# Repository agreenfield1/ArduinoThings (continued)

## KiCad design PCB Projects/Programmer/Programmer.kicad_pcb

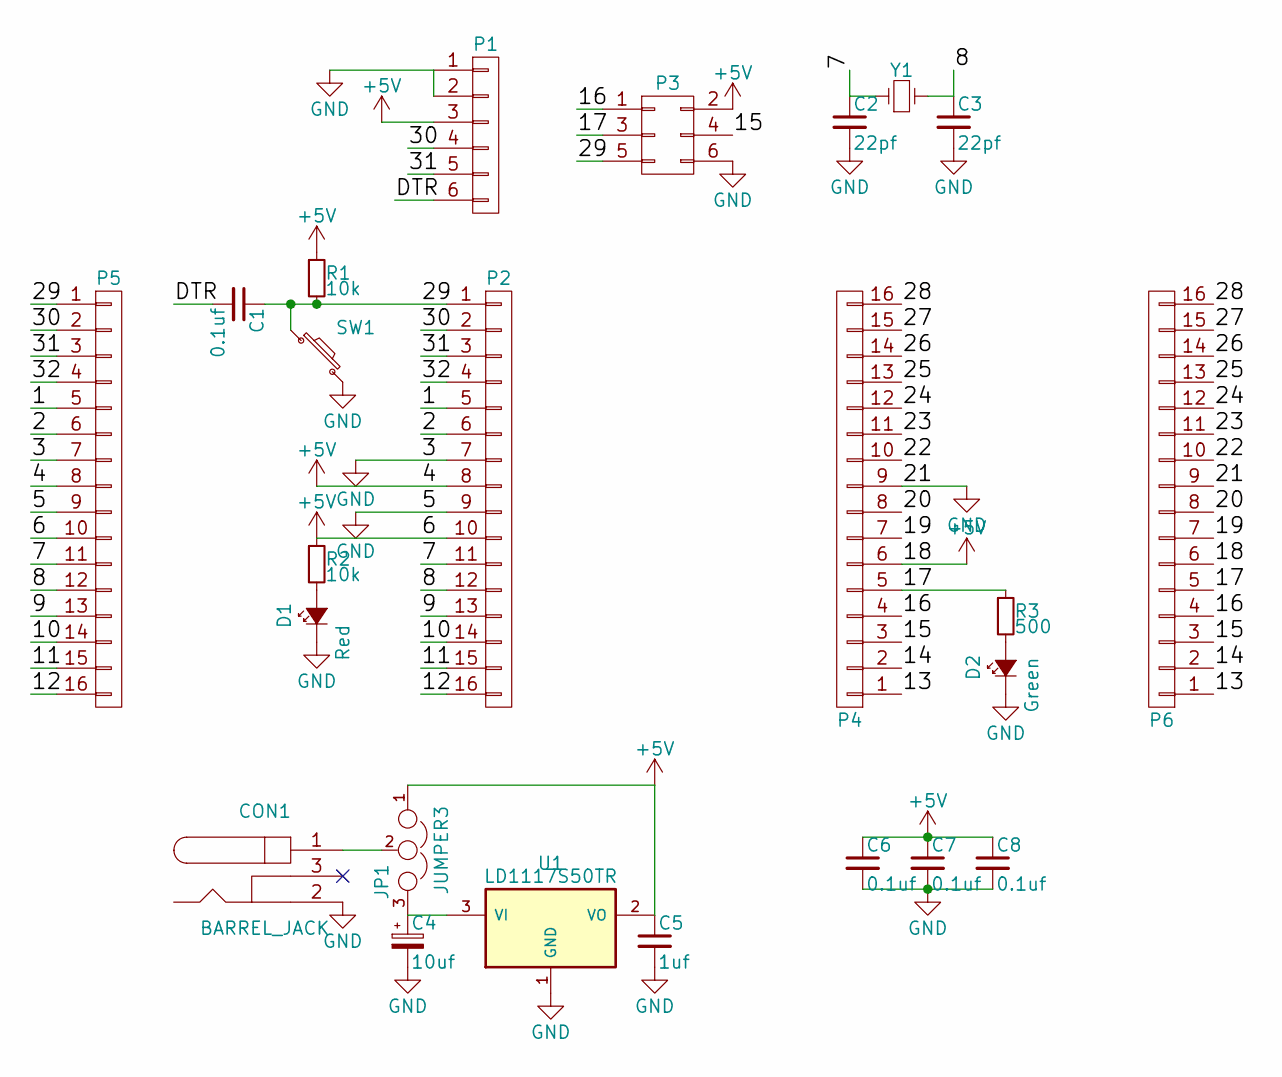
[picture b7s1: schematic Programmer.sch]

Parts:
C1, C6, C7, C8: 0.1uf; C_1206_HandSoldering
C2, C3: 22pf; C_1206_HandSoldering
C4: 10uf; TantalC_SizeA_EIA-3216_HandSoldering
C5: 1uf; C_1206_HandSoldering
CON1: BARREL_JACK; DC-Jack
D1: Red; LED_1206
D2: Green; LED_1206
JP1: JUMPER3; Pin_Header_Straight_1x03
P1: CONN_01X06; Pin_Header_Straight_1x06
P2, P4, P5, P6: CONN_01X16; Pin_Header_Straight_1x16
P3: CONN_02X03; Pin_Header_Straight_2x03
R1, R2: 10k; R_1206_HandSoldering
R3: 500; R_1206_HandSoldering
SW1: SW_PUSH_SMALL; Pin_Header_Angled_1x02
U1: LD1117S50TR; SOT-223
Y1: 22pf; Crystal_HC49-U_Vertical

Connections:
+5V: C5.1, C6.1, C7.1, C8.1, JP1.1, P1.3, P2.8, P2.10, P3.2, P4.6, P5.8, P5.10, P6.6, R1.1, R2.1, U1.2 (VO)
/1: P2.5, P5.5
/2: P2.6, P5.6
/7: C2.1, P2.11, P5.11, Y1.1
/8: C3.1, P2.12, P5.12, Y1.2
/9: P2.13, P5.13
/10: P2.14, P5.14
/11: P2.15, P5.15
/12: P2.16, P5.16
/13: P4.1, P6.1
/14: P4.2, P6.2
/15: P3.4, P4.3, P6.3
/16: P3.1, P4.4, P6.4
/17: P3.3, P4.5, P6.5, R3.1
/19: P4.7, P6.7
/20: P4.8, P6.8
/22: P4.10, P6.10
/23: P4.11, P6.11
/24: P4.12, P6.12
/25: P4.13, P6.13
/26: P4.14, P6.14
/27: P4.15, P6.15
/28: P4.16, P6.16
/29: C1.1, P2.1, P3.5, P5.1, R1.2, SW1.1
/30: P1.4, P2.2, P5.2
/31: P1.5, P2.3, P5.3
/32: P2.4, P5.4
/DTR: C1.2, P1.6
GND: C2.2, C3.2, C4.2, C5.2, C6.2, C7.2, C8.2, CON1.2, D1.1 (K), D2.1 (K), P1.1, P1.2, P2.7, P2.9, P3.6, P4.9, P5.7, P5.9, P6.9, SW1.2, U1.1 (GND)
unnamed: C4.1, JP1.3, U1.3 (VI)
unnamed: CON1.1, JP1.2
unnamed: D1.2 (A), R2.2
unnamed: D2.2 (A), R3.2

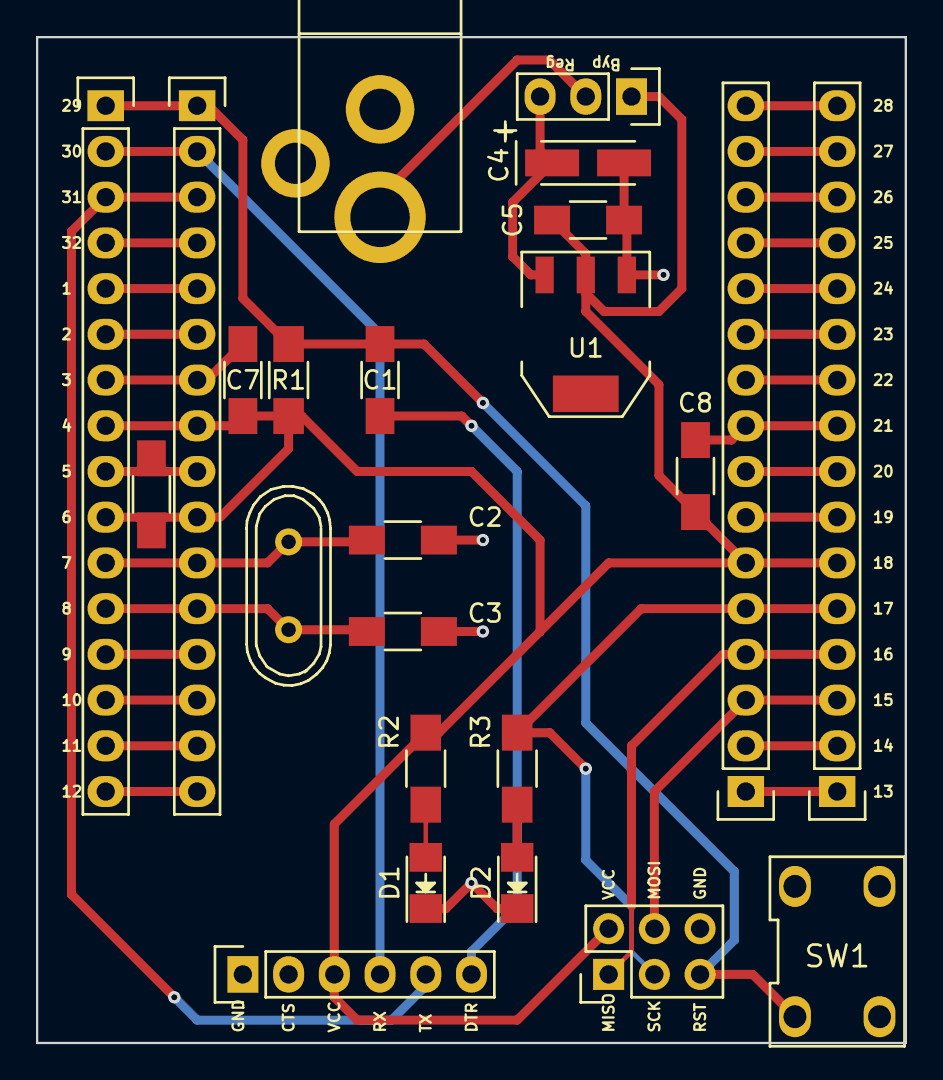
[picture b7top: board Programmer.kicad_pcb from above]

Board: 2 copper layers, 48.3 x 55.9 mm, 24 parts (0 on the bottom side), 33 nets.

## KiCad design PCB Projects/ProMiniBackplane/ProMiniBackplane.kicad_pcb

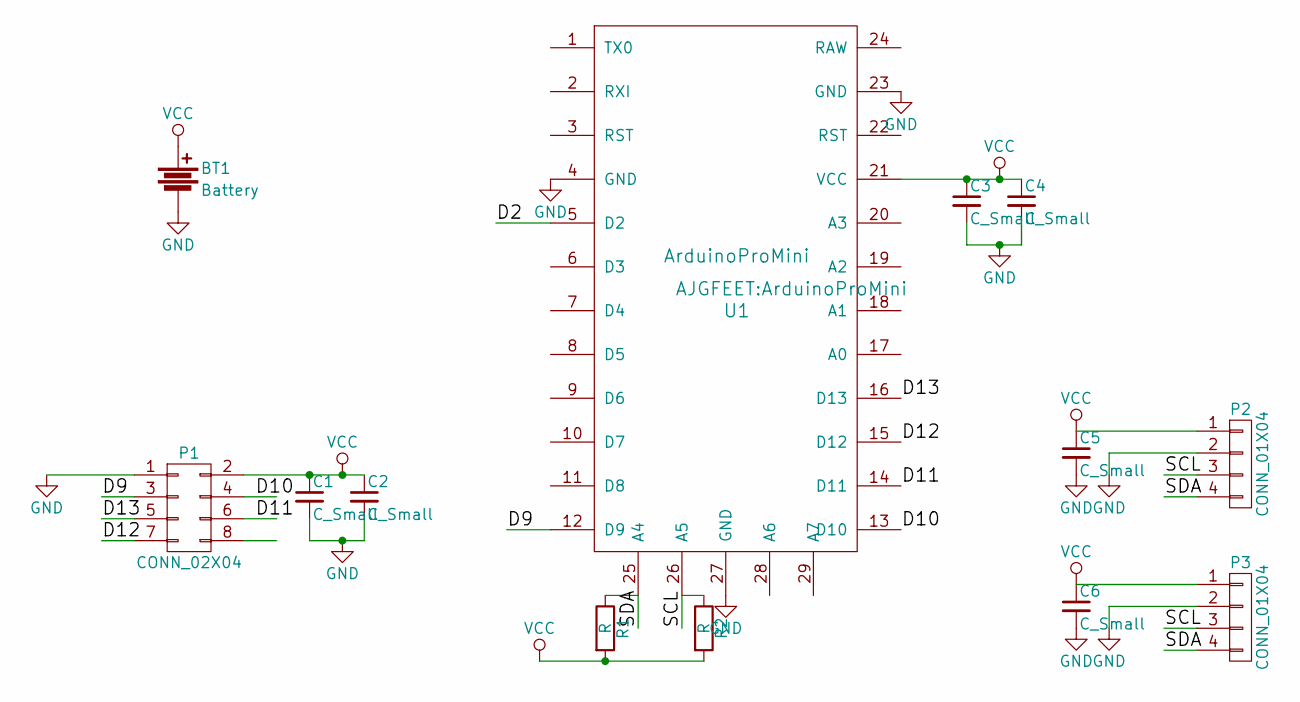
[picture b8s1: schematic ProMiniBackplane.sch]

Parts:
BT1: Battery; CR123Holder
C1, C2, C3, C4, C5, C6: C_Small; C_1206_HandSoldering
P1: CONN_02X04; Pin_Header_Straight_2x04
P2, P3: CONN_01X04; Pin_Header_Straight_1x04
R1, R2: R; R_1206_HandSoldering
U1: ArduinoProMini

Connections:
/D2: U1.5 (D2)
/D9: P1.3, U1.12 (D9)
/D10: P1.4, U1.13 (D10)
/D11: P1.6, U1.14 (D11)
/D12: P1.7, U1.15 (D12)
/D13: P1.5, U1.16 (D13)
/SCL: P2.3, P3.3, R2.1, U1.26 (A5)
/SDA: P2.4, P3.4, R1.1, U1.25 (A4)
GND: BT1.2, C1.2, C2.2, C3.2, C4.2, C5.2, C6.2, P1.1, P2.2, P3.2, U1.4 (GND), U1.23 (GND), U1.27 (GND)
VCC: BT1.1, C1.1, C2.1, C3.1, C4.1, C5.1, C6.1, P1.2, P2.1, P3.1, R1.2, R2.2, U1.21 (VCC)

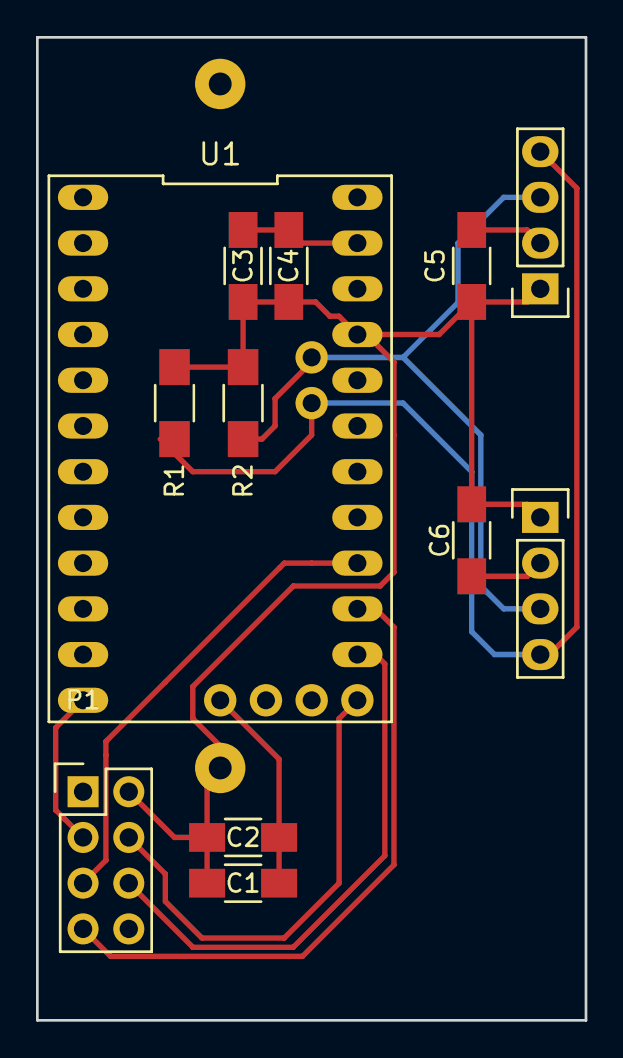
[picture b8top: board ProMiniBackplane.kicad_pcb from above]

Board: 2 copper layers, 30.5 x 54.6 mm, 13 parts (1 on the bottom side), 9 nets.

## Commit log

2016-06-10 First commit?
    ,Yep
2016-06-10 Remove devices and special lib
2016-06-10 Remove extra layers from PCB tempplate
2016-06-11 Added AJGLIB
2016-06-11 Add AJGLIB to template
2016-06-17 More changes
2016-06-19 Tweaks
2016-06-26 More
